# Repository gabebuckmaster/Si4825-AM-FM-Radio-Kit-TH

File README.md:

# Si4825-AM-FM-Radio-Kit-TH
Si4825 AM/FM Radio Kit (Through Hole)

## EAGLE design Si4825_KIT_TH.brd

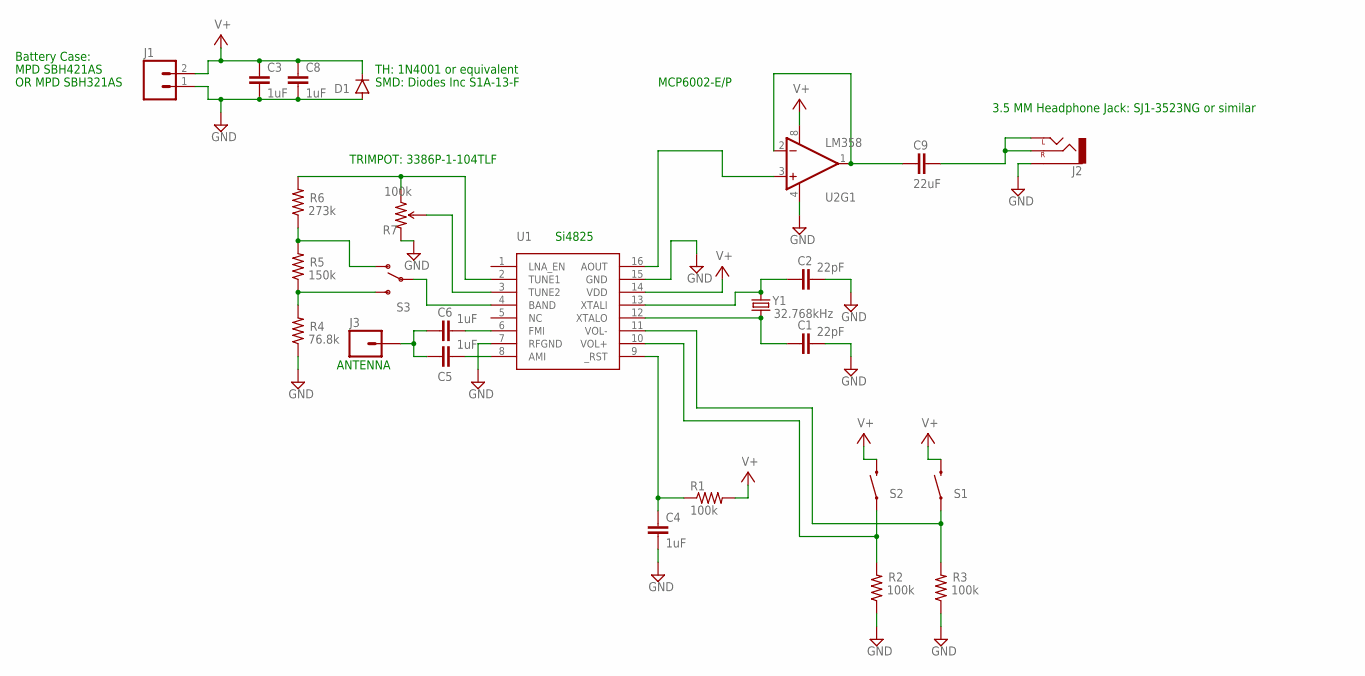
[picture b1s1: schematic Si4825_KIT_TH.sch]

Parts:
C1, C2: 22pF; CAP-PTH-SMALL2
C3, C4, C5, C6, C8: 1uF; AXIAL-5MM
C9: 22uF; AXIAL-5MM
D1: DIODEPTH; DIODE-1N4001
J1: M02PTH; 1X02
J2: AUDIO-JACKPTH; AUDIO-JACK
J3: M01PTH; 1X01
R1, R2, R3: 100k; AXIAL-0.3
R4: 76.8k; AXIAL-0.3
R5: 150k; AXIAL-0.3
R6: 273k; AXIAL-0.3
R7: 100k; BOURNS_3386P
S1, S2: SWITCH-MOMENTARY-2PTH; TACTILE-PTH
S3: SWITCH-SPDTPTH; SWITCH-SPDT
U1: SI4825; SO16
U2: LM358; DIP08
Y1: 32.768kHz; TC26H

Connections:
GND: C1.2, C2.2, C3.P$2 (2), C4.P$2 (2), C8.P$2 (2), D1.A, J1.1, J2.SLEEVE, R2.P$1 (1), R3.P$1 (1), R4.P$1 (1), R7.P$3 (CW), U1.7 (RFGND), U1.15 (GND), U2.4 (V-)
unnamed: C5.P$2 (2), U1.8 (AMI)
unnamed: C1.1, U1.12 (XTALO), Y1.2
unnamed: C2.1, U1.13 (XTALI), Y1.1
unnamed: C4.P$1 (1), R1.P$1 (1), U1.9 (_RST)
unnamed: R2.P$2 (2), S2.1, U1.10 (VOL+)
unnamed: R3.P$2 (2), S1.1, U1.11 (VOL-)
unnamed: S3.2, U1.4 (BAND)
unnamed: R4.P$2 (2), R5.P$1 (1), S3.3 (S)
unnamed: R5.P$2 (2), R6.P$1 (1), S3.1 (O)
unnamed: R6.P$2 (2), R7.P$1 (CCW), U1.2 (TUNE1)
unnamed: C6.P$2 (2), U1.6 (FMI)
unnamed: R7.P$2 (WIPER), U1.3 (TUNE2)
unnamed: C9.P$1 (1), U2.1 (OUT), U2.2 (-IN)
unnamed: U1.16 (AOUT), U2.3 (+IN)
unnamed: C5.P$1 (1), C6.P$1 (1), J3.1
unnamed: C9.P$2 (2), J2.RING (RIGHT), J2.TIP (LEFT)
V+: C3.P$1 (1), C8.P$1 (1), D1.C, J1.2, R1.P$2 (2), S1.3 (2), S2.3 (2), U1.14 (VDD), U2.8 (V+)

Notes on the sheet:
TRIMPOT: 3386P-1-104TLF
MPD SBH421AS
OR MPD SBH321AS
TH: 1N4001 or equivalent
Battery Case:
3.5 MM Headphone Jack: SJ1-3523NG or similar
SMD: Diodes Inc S1A-13-F
ANTENNA
Si4825
MCP6002-E/P

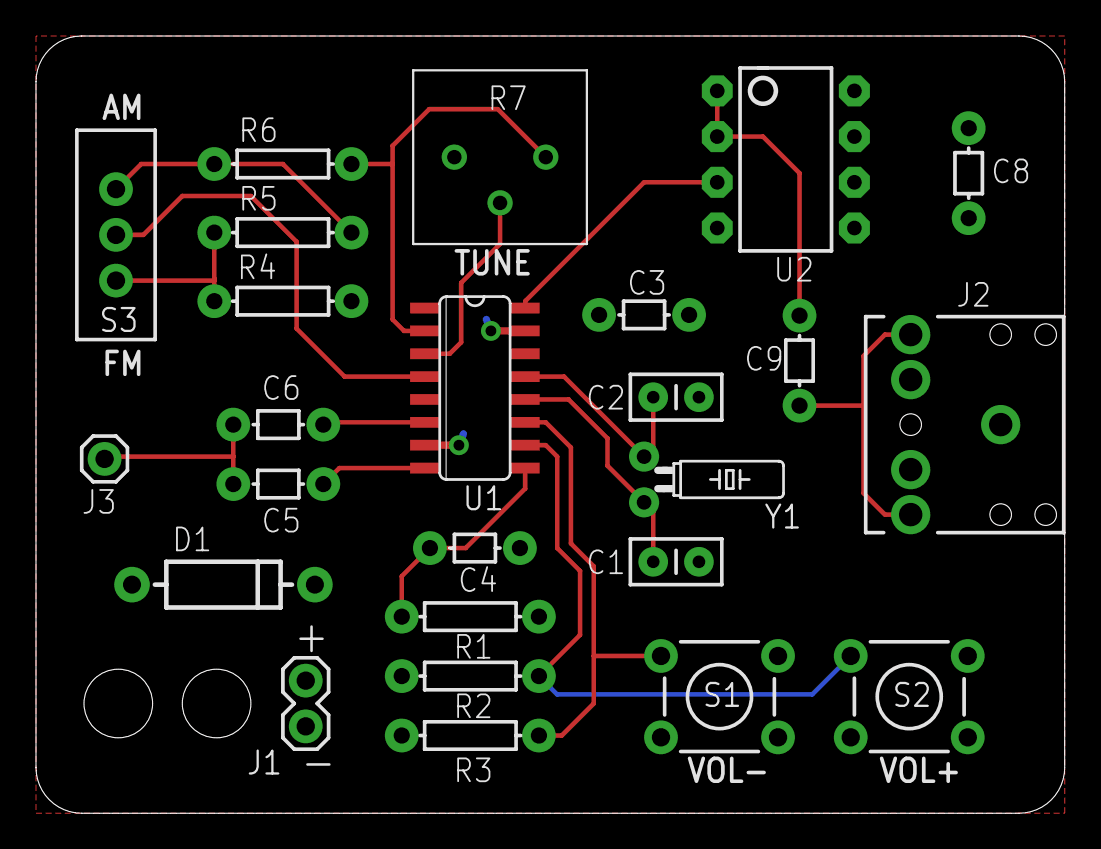
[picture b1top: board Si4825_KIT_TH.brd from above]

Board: 2 copper layers, 57.1 x 43.2 mm, 25 parts (0 on the bottom side), 18 nets.

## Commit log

2016-09-21 Added initial design
2016-10-27 Fixed issues discovered in first build
    - fixed potentiometer footprint
    - bigger strain relief holes: .1” to .15”
    - changed U2 (op amp) to through hole version
    - changed value of C9 (AC coupling capacitor) to 22uF in BOM and
    schematic
    - Removed R8 (jumper to bypass op amp)
2017-04-03 Fixed Typo in BOM
    Line 21 Trough -> Through

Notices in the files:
parts and their libraries:
SparkFun-Connectors: Licensing: Creative Commons ShareAlike 4.0 International - https://creativecommons.org/licenses/by-sa/4.0
